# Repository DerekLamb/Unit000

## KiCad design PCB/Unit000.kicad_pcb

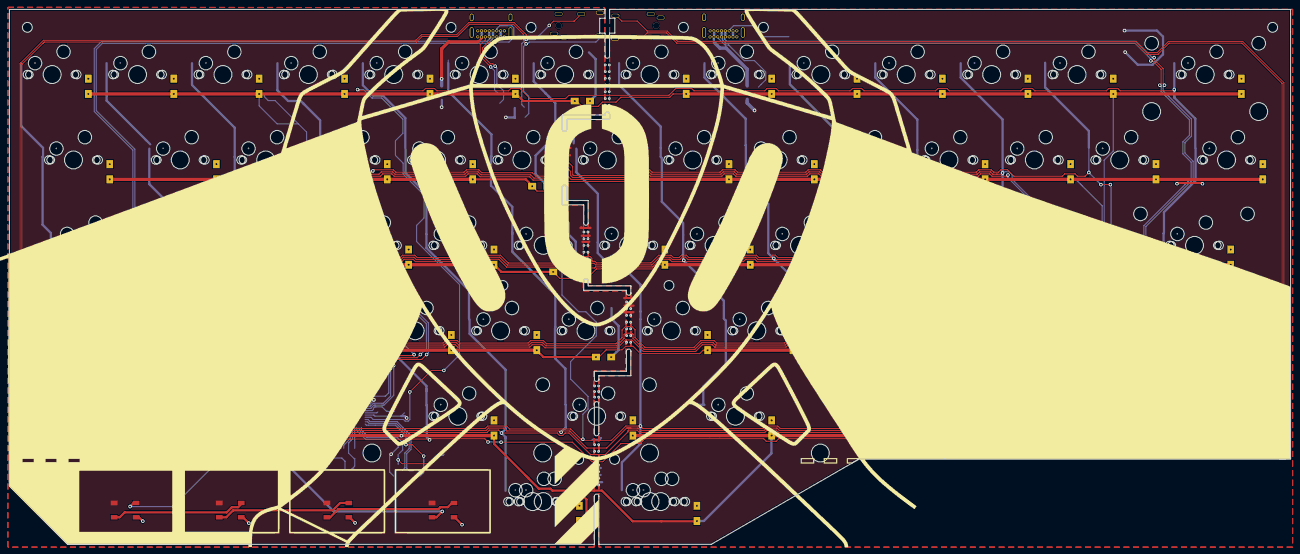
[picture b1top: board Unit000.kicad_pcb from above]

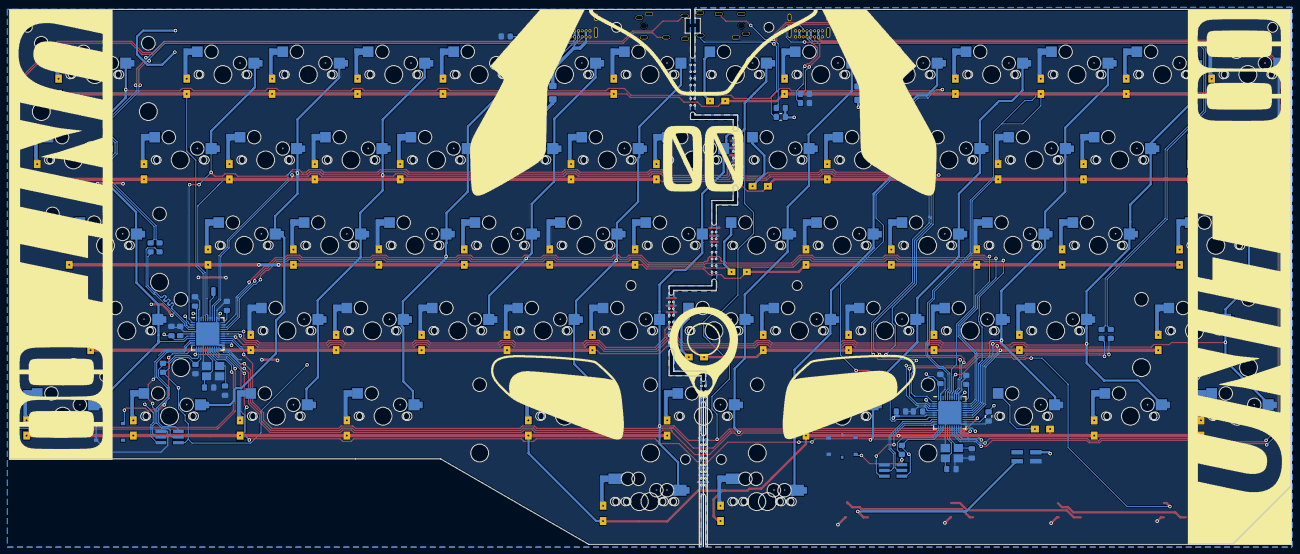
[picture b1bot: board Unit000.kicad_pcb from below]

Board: 2 copper layers, 285.7 x 119.3 mm, 124 parts (39 on the bottom side), 52 nets.

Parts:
C1, C2, C7, C8: 0.1uF; C_0805_2012Metric_Pad1.18x1.45mm_HandSolder
C3, C6, C9, C12: 1uF; C_0805_2012Metric_Pad1.18x1.45mm_HandSolder
C4, C5, C10, C11: 22pF; C_0805_2012Metric_Pad1.18x1.45mm_HandSolder
D1, D2, D3, D4: WS2812B; LED_WS2812B_PLCC4_5.0x5.0mm_P3.2mm_NO_SILK
D1#2, D1#3, D1#4, D1#5, D1#6: Diode; SMD_THT_DIODE_NOSILK
F1, F2: Polyfuse_Small; Fuse_1206_3216Metric_Pad1.42x1.75mm_HandSolder
GRV1: MXSocketDioded; CherryMX_Hotswap_SingleSide_Diode_NO_SILK
J1, J2: AudioJack4; TENSILITY_54-00176
J3, J4: Conn_01x06_Male; PinHeader_2x03_P1.27mm_Vertical_SMD
J5: Conn_01x03_Male; PinHeader_2x02_P2.00mm_Vertical_SMD
K_1: SW_Push; CherryMX_Hotswap_SingleSide_Diode_NO_SILK
P1, P2: USB_C_Plug_USB2.0; USB_C_Receptacle_GCT_USB4085
R1, R4, R5, R8: 10k; R_0805_2012Metric_Pad1.20x1.40mm_HandSolder
R2, R3, R13, R14: 22; R_0805_2012Metric_Pad1.20x1.40mm_HandSolder
R6, R7, R9, R10, R11, R12: 4.7k; R_0805_2012Metric_Pad1.20x1.40mm_HandSolder
Ref**: Val**; Finalized_Part2_2
ST14, ST41, ST42, ST53: MountingHole; Stabilizer_Cherry_MX_2u
ST58, ST59: MountingHole; Stabilizer_Cherry_MX_3u
SW1, SW2: SW_Push; PTS526_SKG15_SMTR2 LFS
SW3, SW4, SW5, SW6, SW8, SW9, SW10, SW11, SW12, SW13, SW14, SW15, SW16, SW17, SW18, SW19, SW21, SW22, SW23, SW24, SW25, SW26, SW27, SW28, SW29, SW30, SW31, SW32, SW33, SW35, SW36, SW37, SW38, SW39, SW40, SW41, SW42, SW43, SW44, SW45, SW46, SW48, SW49, SW50, SW51, SW52, SW53, SW54, SW55, SW57, SW58, SW59, SW60, SW61, SW62, SW63, SW65, SW66: SW_Push; CherryMX_Hotswap_SingleSide_Diode_NO_SILK
SW7, SW20, SW34, SW47, SW56, SW64, SW67: SW_Push; CherryMX_Hotswap_SingleSide_NO_DIODE_NO_SILK
U1, U2: ATmega32U4-MU; QFN-44-1EP_7x7mm_P0.5mm_EP5.2x5.2mm
Y1, Y2: 16MHz; Crystal_SMD_3225-4Pin_3.2x2.5mm_HandSoldering

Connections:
+5V: C1.2, C2.2, C3.2, C7.2, C8.2, C9.2, D1.1, D2.1, D3.1, D4.1, F1.1, F2.1, J1.S, J2.S, J3.1, J4.1, J5.3, R1.2, R5.2, R6.2, R7.2, U1.2, U1.7, U1.14, U1.24, U1.34, U1.44, U2.2, U2.7, U2.14, U2.24, U2.34, U2.44
Col0: GRV1.1, SW15.1, SW29.1, SW42.1, SW54.1, U1.27, U2.27
Col1: K_1.1, SW16.1, SW30.1, SW43.1, SW55.1, U1.28, U2.28
Col2: SW3.1, SW17.1, SW31.1, SW44.1, SW56.1, U1.29, U2.29
Col3: SW4.1, SW18.1, SW32.1, SW45.1, SW58.1, U1.20, U2.20
Col4: SW5.1, SW19.1, SW33.1, SW46.1, SW64.1, SW65.1, U1.21, U2.21
Col5: SW6.1, SW20.1, SW34.1, SW47.1, SW57.1, U1.22, U2.22
Col6: SW7.1, SW21.1, SW35.1, SW48.1, SW66.1, SW67.1, U1.25, U2.25
Col7: SW8.1, SW22.1, SW36.1, SW49.1, SW59.1, U1.30, U2.30
Col8: SW9.1, SW23.1, SW37.1, SW50.1, U1.31, U2.31
Col9: SW10.1, SW24.1, SW38.1, SW51.1, SW60.1, U1.32, U2.32
Col10: SW11.1, SW25.1, SW39.1, SW52.1, SW61.1, U1.36, U2.36
Col11: SW12.1, SW26.1, SW40.1, SW62.1, U1.37, U2.37
Col12: SW13.1, SW27.1, U1.1, U2.1
Col13: SW14.1, SW28.1, SW41.1, SW53.1, SW63.1, U1.8, U2.8
D+: P1.A6, P1.B7, P2.A6, P2.B7, R2.2, R13.2
D-: P1.A7, P1.B6, P2.A7, P2.B6, R3.2, R14.2
GND: C1.1, C2.1, C3.1, C4.2, C5.2, C6.2, C7.1, C8.1, C9.1, C10.2, C11.2, C12.2, D1.3, D2.3, D3.3, D4.3, J1.T, J2.T, J3.6, J4.6, J5.1, P1.A1, P1.A12, P1.B1, P1.B12, P1.S1, P2.A1, P2.A12, P2.B1, P2.B12, P2.S1, R4.1, R8.1, R9.1, R10.1, R11.1, R12.1, SW1.1, SW2.1, U1.5, U1.15, U1.23, U1.35, U1.43, U1.45, U2.5, U2.15, U2.23, U2.35, U2.43, U2.45, Y1.2, Y1.4, Y2.2, Y2.4
MISO: J3.2, J4.2, U1.11, U2.11
MOSI: J3.3, J4.3, U1.10, U2.10
unnamed: C4.1, U1.17, Y1.1
unnamed: C5.1, U1.16, Y1.3
unnamed: C6.1, U1.6
unnamed: C10.1, U2.17, Y2.1
unnamed: C11.1, U2.16, Y2.3
unnamed: C12.1, U2.6
unnamed: D1.2, D2.4
unnamed: D2.2, D3.4
unnamed: D3.2, D4.4
unnamed: D4.2, J5.2
unnamed: F1.2, P1.A4, P1.A9, P1.B4, P1.B9
unnamed: F2.2, P2.A4, P2.A9, P2.B4, P2.B9
unnamed: P1.A5, R9.2
unnamed: P1.B5, R10.2
unnamed: P2.A5, R11.2
unnamed: P2.B5, R12.2
unnamed: R2.1, U1.4
unnamed: R3.1, U1.3
unnamed: R4.2, U1.33
unnamed: R8.2, U2.33
unnamed: R13.1, U2.4
unnamed: R14.1, U2.3
RESET: J3.5, J4.5, R1.1, R5.1, SW1.2, SW2.2, U1.13, U2.13
RGBLED: D1.4, U1.38, U2.38
Row0: D1#3.2, GRV1.2, K_1.2, SW3.2, SW4.2, SW5.2, SW6.2, SW8.2, SW9.2, SW10.2, SW11.2, SW12.2, SW13.2, SW14.2, U1.41, U2.41
Row1: D1#4.2, SW15.2, SW16.2, SW17.2, SW18.2, SW19.2, SW21.2, SW22.2, SW23.2, SW24.2, SW25.2, SW26.2, SW27.2, SW28.2, U1.40, U2.40
Row2: D1#5.2, SW29.2, SW30.2, SW31.2, SW32.2, SW33.2, SW35.2, SW36.2, SW37.2, SW38.2, SW39.2, SW40.2, SW41.2, U1.39, U2.39
Row3: D1#6.2, SW42.2, SW43.2, SW44.2, SW45.2, SW46.2, SW48.2, SW49.2, SW50.2, SW51.2, SW52.2, SW53.2, U1.26, U2.26
Row4: D1#2.2, SW54.2, SW55.2, SW57.2, SW58.2, SW59.2, SW60.2, SW61.2, SW62.2, SW63.2, SW65.2, SW66.2, U1.12, U2.12
SCK: J3.4, J4.4, U1.9, U2.9
SCL: J1.R1, J2.R1, R6.1, U1.18, U2.18
SDA: J1.R2, J2.R2, R7.1, U1.19, U2.19

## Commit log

2023-07-18 Initial commit Still missing config files
    Initial commit

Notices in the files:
parts and their libraries:
Copyright 2021 Accelerated Designs. All rights reserved.
